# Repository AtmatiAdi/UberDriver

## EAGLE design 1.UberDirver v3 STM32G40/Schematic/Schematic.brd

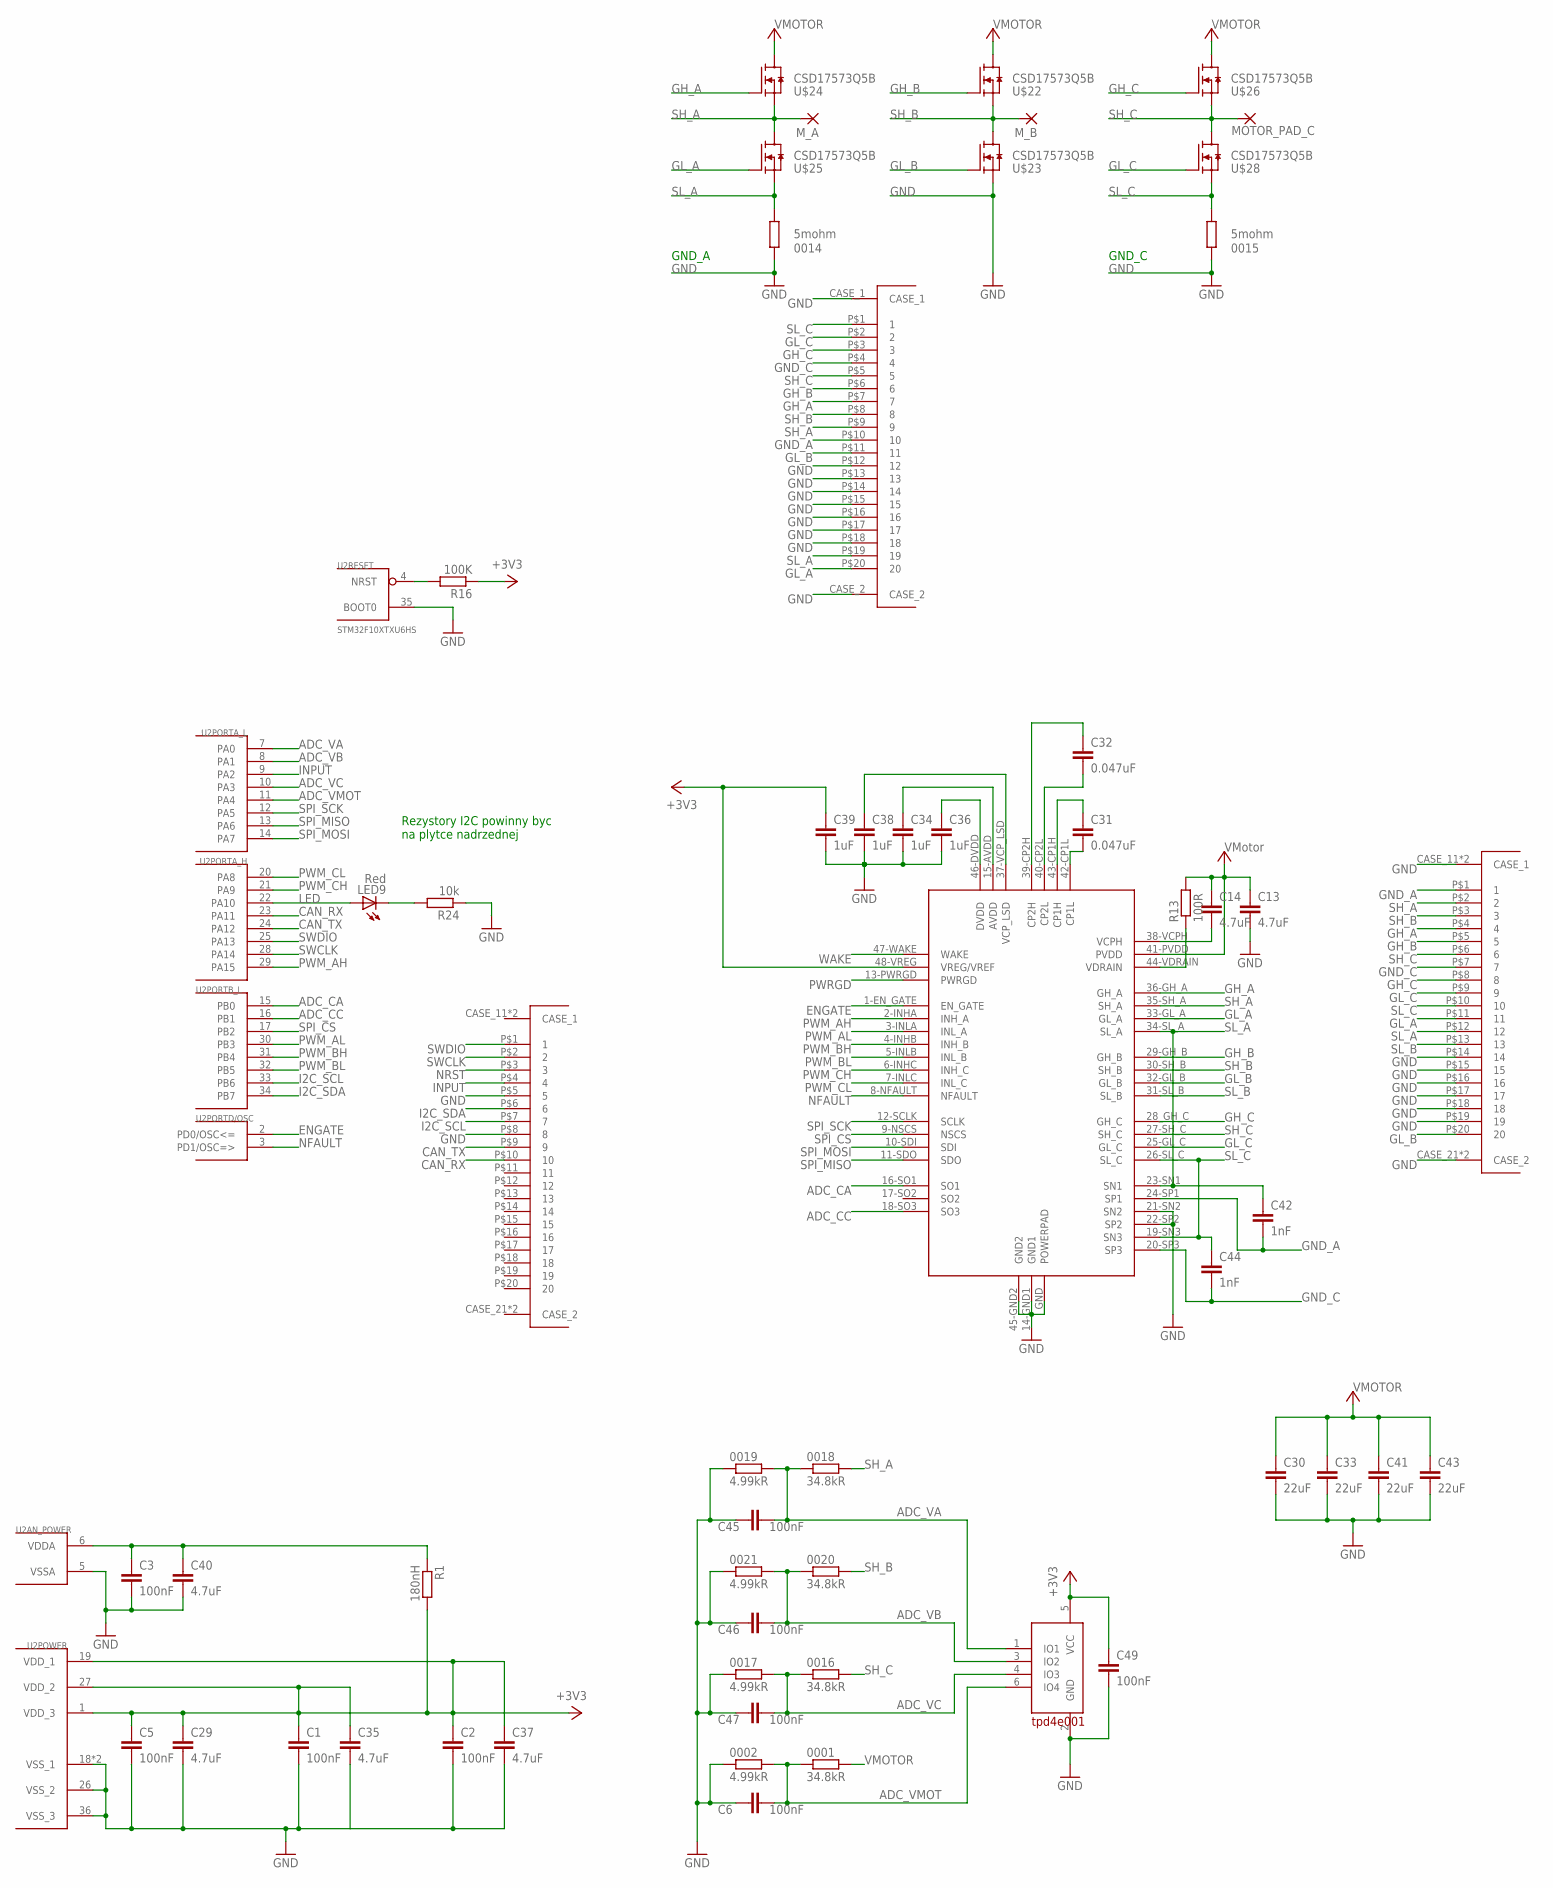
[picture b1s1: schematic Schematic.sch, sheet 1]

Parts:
0001, 0016, 0018, 0020: 34.8kR; R0402
0002, 0017, 0019, 0021: 4.99kR; R0402
0014, 0015: 5mohm; R2512
C1, C2, C3, C5, C6, C45, C46, C47, C49: 100nF; R0402
C13, C14: 4.7uF; C0805
C29, C35, C37, C40: 4.7uF; R0402
C30, C33, C41, C43: 22uF; C1206
C31, C32: 0.047uF; R0402
C34, C36, C38, C39: 1uF; R0402
C42, C44: 1nF; R0402
LED9: Red; SML0603
MOTOR_PAD_C: SMD5; SMD2,54-5,08
M_A: SMD5; SMD2,54-5,08
M_B: SMD5; SMD2,54-5,08
R1: 180nH; R0603
R13: 100R; R0603
R16: 100K; R0402
R24: 10k; R0402
U2: STM32F10XTXU6HS; VFQFPN36-HS
U$1, U$32: RECEPTACLE_20_0.4_5024262030
U$21: DRV8305; S-PQFP-G48
U$22, U$23, U$24, U$25, U$26, U$28: CSD17573Q5B; Q5B
U$30: PLUG_20_0.4_5024302012
U$31: TPD4E001; SOT-23

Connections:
+3V3: C1.1, C2.1, C5.1, C29.1, C35.1, C37.1, C39.1, C49.1, R1.2, R16.1, U2.1 (VDD_3), U2.19 (VDD_1), U2.27 (VDD_2), U$21.48-VREG (VREG/VREF), U$31.5 (VCC)
ADC_CA: U2.15 (PB0), U$21.16-SO1 (SO1)
ADC_CC: U2.16 (PB1), U$21.18-SO3 (SO3)
ADC_VA: 0018.1, 0019.2, C45.1, U2.7 (PA0), U$31.1 (IO1)
ADC_VB: 0020.1, 0021.2, C46.1, U2.8 (PA1), U$31.3 (IO2)
ADC_VC: 0016.1, 0017.2, C47.1, U2.10 (PA3), U$31.4 (IO3)
ADC_VMOT: 0001.1, 0002.2, C6.1, U2.11 (PA4), U$31.6 (IO4)
CAN_RX: U2.23 (PA11), U$1.P$10 (10)
CAN_TX: U2.24 (PA12), U$1.P$9 (9)
ENGATE: U2.2 (PD0/OSC<=), U$21.1-EN_GATE (EN_GATE)
GH_A: U$21.36-GH_A (GH_A), U$24.G, U$30.P$7 (7), U$32.P$4 (4)
GH_B: U$21.29-GH_B (GH_B), U$22.G, U$30.P$6 (6), U$32.P$5 (5)
GH_C: U$21.28_GH_C (GH_C), U$26.G, U$30.P$3 (3), U$32.P$8 (8)
GL_A: U$21.33-GL_A (GL_A), U$25.G, U$30.P$20 (20), U$32.P$11 (11)
GL_B: U$21.32-GL_B (GL_B), U$23.G, U$30.P$11 (11), U$32.P$20 (20)
GL_C: U$21.25-GL_C (GL_C), U$28.G, U$30.P$2 (2), U$32.P$9 (9)
GND: 0002.1, 0014.1, 0015.1, 0017.1, 0019.1, 0021.1, C1.2, C2.2, C3.2, C5.2, C6.2, C13.2, C29.2, C30.2, C33.2, C34.2, C35.2, C36.2, C37.2, C38.2, C39.2, C40.2, C41.2, C43.2, C45.2, C46.2, C47.2, C49.2, R24.1, U2.5 (VSSA), U2.18 (VSS_1), U2.26 (VSS_2), U2.35 (BOOT0), U2.36 (VSS_3), U2.GND (VSS_1), U$1.P$5 (5), U$1.P$8 (8), U$21.14-GND1 (GND1), U$21.21-SN2 (SN2), U$21.22-SP2 (SP2), U$21.45-GND2 (GND2), U$21.GND (POWERPAD), U$23.S, U$30.CASE_1, U$30.CASE_2, U$30.P$12 (12), U$30.P$13 (13), U$30.P$14 (14), U$30.P$15 (15), U$30.P$16 (16), U$30.P$17 (17), U$30.P$18 (18), U$31.2 (GND), U$32.CASE_11 (CASE_1), U$32.CASE_12 (CASE_1), U$32.CASE_21 (CASE_2), U$32.CASE_22 (CASE_2), U$32.P$14 (14), U$32.P$15 (15), U$32.P$16 (16), U$32.P$17 (17), U$32.P$18 (18), U$32.P$19 (19)
GND_A: C42.2, U$21.24-SP1 (SP1), U$30.P$10 (10), U$32.P$1 (1)
GND_C: C44.2, U$21.20-SP3 (SP3), U$30.P$4 (4), U$32.P$7 (7)
I2C_SCL: U2.33 (PB6), U$1.P$7 (7)
I2C_SDA: U2.34 (PB7), U$1.P$6 (6)
INPUT: U2.9 (PA2), U$1.P$4 (4)
LED: LED9.A, U2.22 (PA10)
unnamed: C3.1, C40.1, R1.1, U2.6 (VDDA)
unnamed: C36.1, U$21.46-DVDD (DVDD)
unnamed: C34.1, U$21.15-AVDD (AVDD)
unnamed: C38.1, U$21.37-VCP_LSD (VCP_LSD)
unnamed: C31.2, U$21.42-CP1L (CP1L)
unnamed: C31.1, U$21.43-CP1H (CP1H)
unnamed: C32.2, U$21.40-CP2L (CP2L)
unnamed: C32.1, U$21.39-CP2H (CP2H)
unnamed: R13.1, U$21.44-VDRAIN (VDRAIN)
unnamed: C14.2, U$21.38-VCPH (VCPH)
unnamed: LED9.C, R24.2
NFAULT: U2.3 (PD1/OSC=>), U$21.8-NFAULT (NFAULT)
NRST: R16.2, U2.4 (NRST), U$1.P$3 (3)
PWM_AH: U2.29 (PA15), U$21.2-INHA (INH_A)
PWM_AL: U2.30 (PB3), U$21.3-INLA (INL_A)
PWM_BH: U2.31 (PB4), U$21.4-INHB (INH_B)
PWM_BL: U2.32 (PB5), U$21.5-INLB (INL_B)
PWM_CH: U2.21 (PA9), U$21.6-INHC (INH_C)
PWM_CL: U2.20 (PA8), U$21.7-INLC (INL_C)
PWRGD: U$21.13-PWRGD (PWRGD)
SH_A: 0018.2, M_A.1, U$21.35-SH_A (SH_A), U$24.S, U$25.D, U$30.P$9 (9), U$32.P$2 (2)
SH_B: 0020.2, M_B.1, U$21.30-SH_B (SH_B), U$22.S, U$23.D, U$30.P$8 (8), U$32.P$3 (3)
SH_C: 0016.2, MOTOR_PAD_C.1, U$21.27-SH_C (SH_C), U$26.S, U$28.D, U$30.P$5 (5), U$32.P$6 (6)
SL_A: 0014.2, C42.1, U$21.23-SN1 (SN1), U$21.34-SL_A (SL_A), U$25.S, U$30.P$19 (19), U$32.P$12 (12)
SL_B: U$21.31-SL_B (SL_B), U$32.P$13 (13)
SL_C: 0015.2, C44.1, U$21.19-SN3 (SN3), U$21.26-SL_C (SL_C), U$28.S, U$30.P$1 (1), U$32.P$10 (10)
SPI_CS: U2.17 (PB2), U$21.9-NSCS (NSCS)
SPI_MISO: U2.13 (PA6), U$21.11-SDO (SDO)
SPI_MOSI: U2.14 (PA7), U$21.10-SDI (SDI)
SPI_SCK: U2.12 (PA5), U$21.12-SCLK (SCLK)
SWCLK: U2.28 (PA14), U$1.P$2 (2)
SWDIO: U2.25 (PA13), U$1.P$1 (1)
VMOTOR: 0001.2, C13.1, C14.1, C30.1, C33.1, C41.1, C43.1, R13.2, U$21.41-PVDD (PVDD), U$22.D, U$24.D, U$26.D
WAKE: U$21.47-WAKE (WAKE)

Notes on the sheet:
Rezystory I2C powinny byc na plytce nadrzednej
GND_A
GND_C

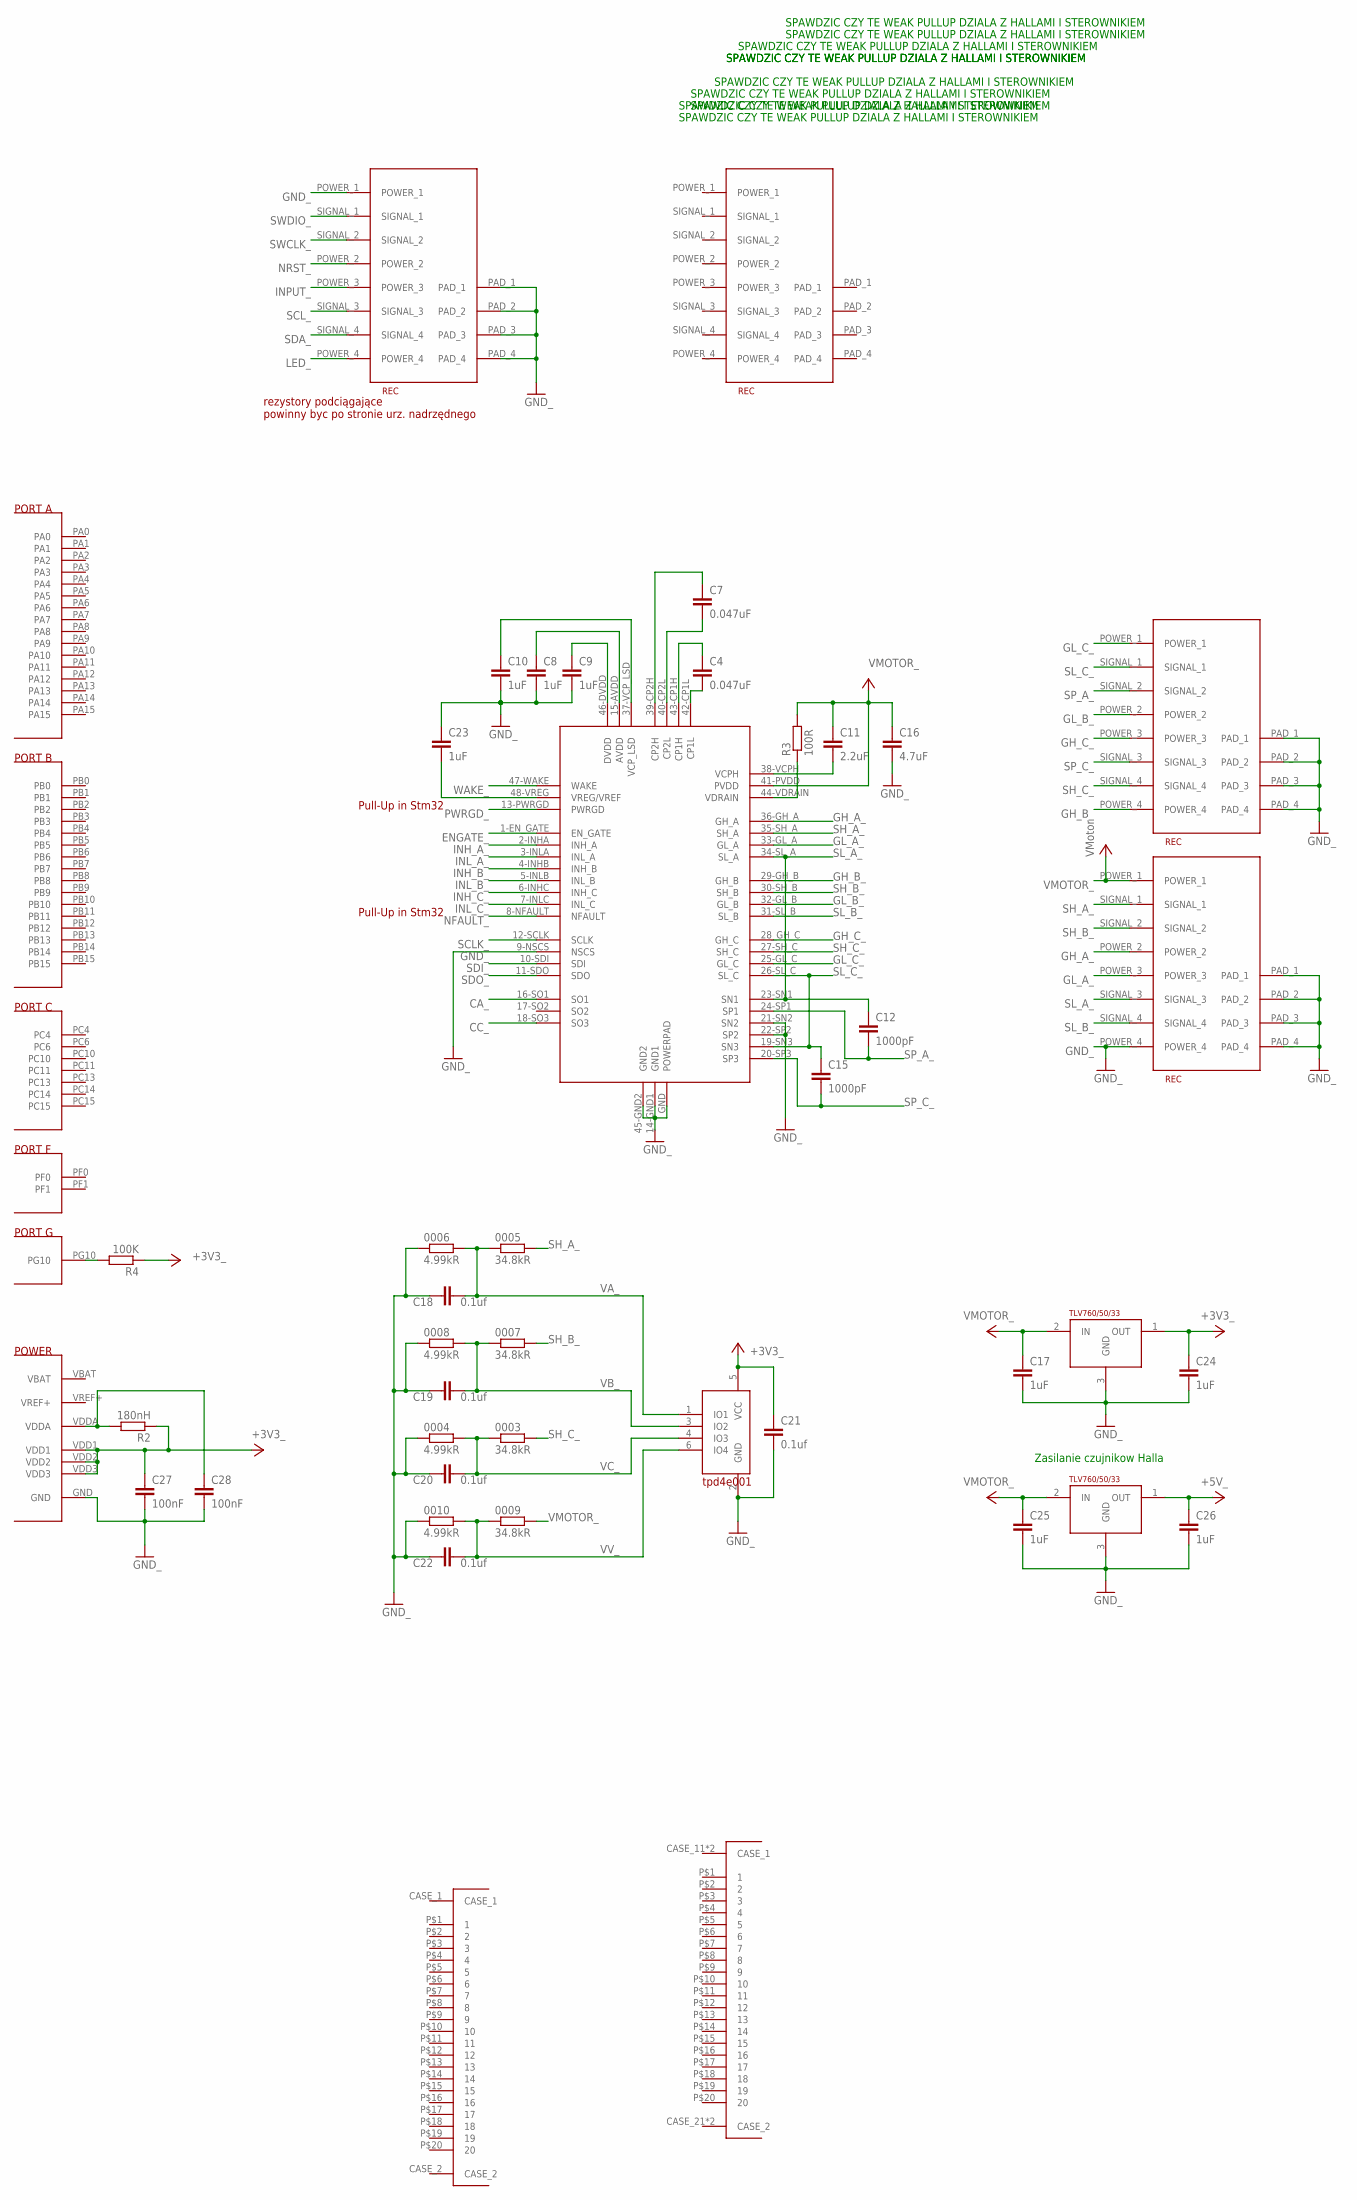
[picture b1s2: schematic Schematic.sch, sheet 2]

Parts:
0003, 0005, 0007, 0009: 34.8kR; R0402
0004, 0006, 0008, 0010: 4.99kR; R0402
C4, C7: 0.047uF; C0603
C8, C9, C10, C17, C23, C24, C25, C26: 1uF; C0603
C11: 2.2uF; C0603
C12, C15: 1000pF; C0603
C16: 4.7uF; C0805
C18, C19, C20, C22: 0.1uf; C0402
C21: 0.1uf; C0603
C27, C28: 100nF; C0603
R2: 180nH; R0603
R3: 100R; R0603
R4: 100K; R0603
U$12: STM32G473CC; VFQFPN36
U$13: DRV8305; S-PQFP-G48
U$14, U$15, U$18, U$19: MOLEG_REC_8X0.4MM; REC
U$16: TPD4E001; SOT-23
U$17, U$20: TLV760XX; SOT-23-3
U$27: PLUG_20_0.4_5024302012
U$29: RECEPTACLE_20_0.4_5024262030

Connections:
+3V3_: C21.1, C24.1, C27.1, R2.1, R4.1, U$12.VDD1, U$12.VDD2, U$12.VDD3, U$16.5 (VCC), U$17.1 (OUT)
+5V_: C26.1, U$20.1 (OUT)
CA_: U$13.16-SO1 (SO1)
CC_: U$13.18-SO3 (SO3)
ENGATE_: U$13.1-EN_GATE (EN_GATE)
GH_A_: U$13.36-GH_A (GH_A), U$15.POWER_2
GH_B_: U$13.29-GH_B (GH_B), U$14.POWER_4
GH_C_: U$13.28_GH_C (GH_C), U$14.POWER_3
GL_A_: U$13.33-GL_A (GL_A), U$15.POWER_3
GL_B_: U$13.32-GL_B (GL_B), U$14.POWER_2
GL_C_: U$13.25-GL_C (GL_C), U$14.POWER_1
GND_: 0004.1, 0006.1, 0008.1, 0010.1, C8.2, C9.2, C10.2, C16.2, C17.2, C18.2, C19.2, C20.2, C21.2, C22.2, C23.1, C24.2, C25.2, C26.2, C27.2, C28.2, U$12.GND, U$13.9-NSCS (NSCS), U$13.14-GND1 (GND1), U$13.21-SN2 (SN2), U$13.22-SP2 (SP2), U$13.45-GND2 (GND2), U$13.GND (POWERPAD), U$14.PAD_1, U$14.PAD_2, U$14.PAD_3, U$14.PAD_4, U$15.PAD_1, U$15.PAD_2, U$15.PAD_3, U$15.PAD_4, U$15.POWER_4, U$16.2 (GND), U$17.3 (GND), U$18.PAD_1, U$18.PAD_2, U$18.PAD_3, U$18.PAD_4, U$18.POWER_1, U$20.3 (GND)
INH_A_: U$13.2-INHA (INH_A)
INH_B_: U$13.4-INHB (INH_B)
INH_C_: U$13.6-INHC (INH_C)
INL_A_: U$13.3-INLA (INL_A)
INL_B_: U$13.5-INLB (INL_B)
INL_C_: U$13.7-INLC (INL_C)
INPUT_: U$18.POWER_3
LED_: U$18.POWER_4
unnamed: C9.1, U$13.46-DVDD (DVDD)
unnamed: C8.1, U$13.15-AVDD (AVDD)
unnamed: C10.1, U$13.37-VCP_LSD (VCP_LSD)
unnamed: C4.2, U$13.42-CP1L (CP1L)
unnamed: C4.1, U$13.43-CP1H (CP1H)
unnamed: C7.2, U$13.40-CP2L (CP2L)
unnamed: C7.1, U$13.39-CP2H (CP2H)
unnamed: R3.1, U$13.44-VDRAIN (VDRAIN)
unnamed: C11.2, U$13.38-VCPH (VCPH)
unnamed: C23.2, U$13.48-VREG (VREG/VREF)
unnamed: R4.2, U$12.PG10
unnamed: C28.1, R2.2, U$12.VDDA
NFAULT_: U$13.8-NFAULT (NFAULT)
NRST_: U$18.POWER_2
PWRGD_: U$13.13-PWRGD (PWRGD)
SCLK_: U$13.12-SCLK (SCLK)
SCL_: U$18.SIGNAL_3
SDA_: U$18.SIGNAL_4
SDI_: U$13.10-SDI (SDI)
SDO_: U$13.11-SDO (SDO)
SH_A_: 0005.2, U$13.35-SH_A (SH_A), U$15.SIGNAL_1
SH_B_: 0007.2, U$13.30-SH_B (SH_B), U$15.SIGNAL_2
SH_C_: 0003.2, U$13.27-SH_C (SH_C), U$14.SIGNAL_4
SL_A_: C12.1, U$13.23-SN1 (SN1), U$13.34-SL_A (SL_A), U$15.SIGNAL_3
SL_B_: U$13.31-SL_B (SL_B), U$15.SIGNAL_4
SL_C_: C15.1, U$13.19-SN3 (SN3), U$13.26-SL_C (SL_C), U$14.SIGNAL_1
SP_A_: C12.2, U$13.24-SP1 (SP1), U$14.SIGNAL_2
SP_C_: C15.2, U$13.20-SP3 (SP3), U$14.SIGNAL_3
SWCLK_: U$18.SIGNAL_2
SWDIO_: U$18.SIGNAL_1
VA_: 0005.1, 0006.2, C18.1, U$16.1 (IO1)
VB_: 0007.1, 0008.2, C19.1, U$16.3 (IO2)
VC_: 0003.1, 0004.2, C20.1, U$16.4 (IO3)
VMOTOR_: 0009.2, C11.1, C16.1, C17.1, C25.1, R3.2, U$13.41-PVDD (PVDD), U$15.POWER_1, U$17.2 (IN), U$20.2 (IN)
VV_: 0009.1, 0010.2, C22.1, U$16.6 (IO4)
WAKE_: U$13.47-WAKE (WAKE)

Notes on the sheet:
Pull-Up in Stm32
rezystory podciągające powinny byc po stronie urz. nadrzędnego
Zasilanie czujnikow Halla
SPAWDZIC CZY TE WEAK PULLUP DZIALA Z HALLAMI I STEROWNIKIEM

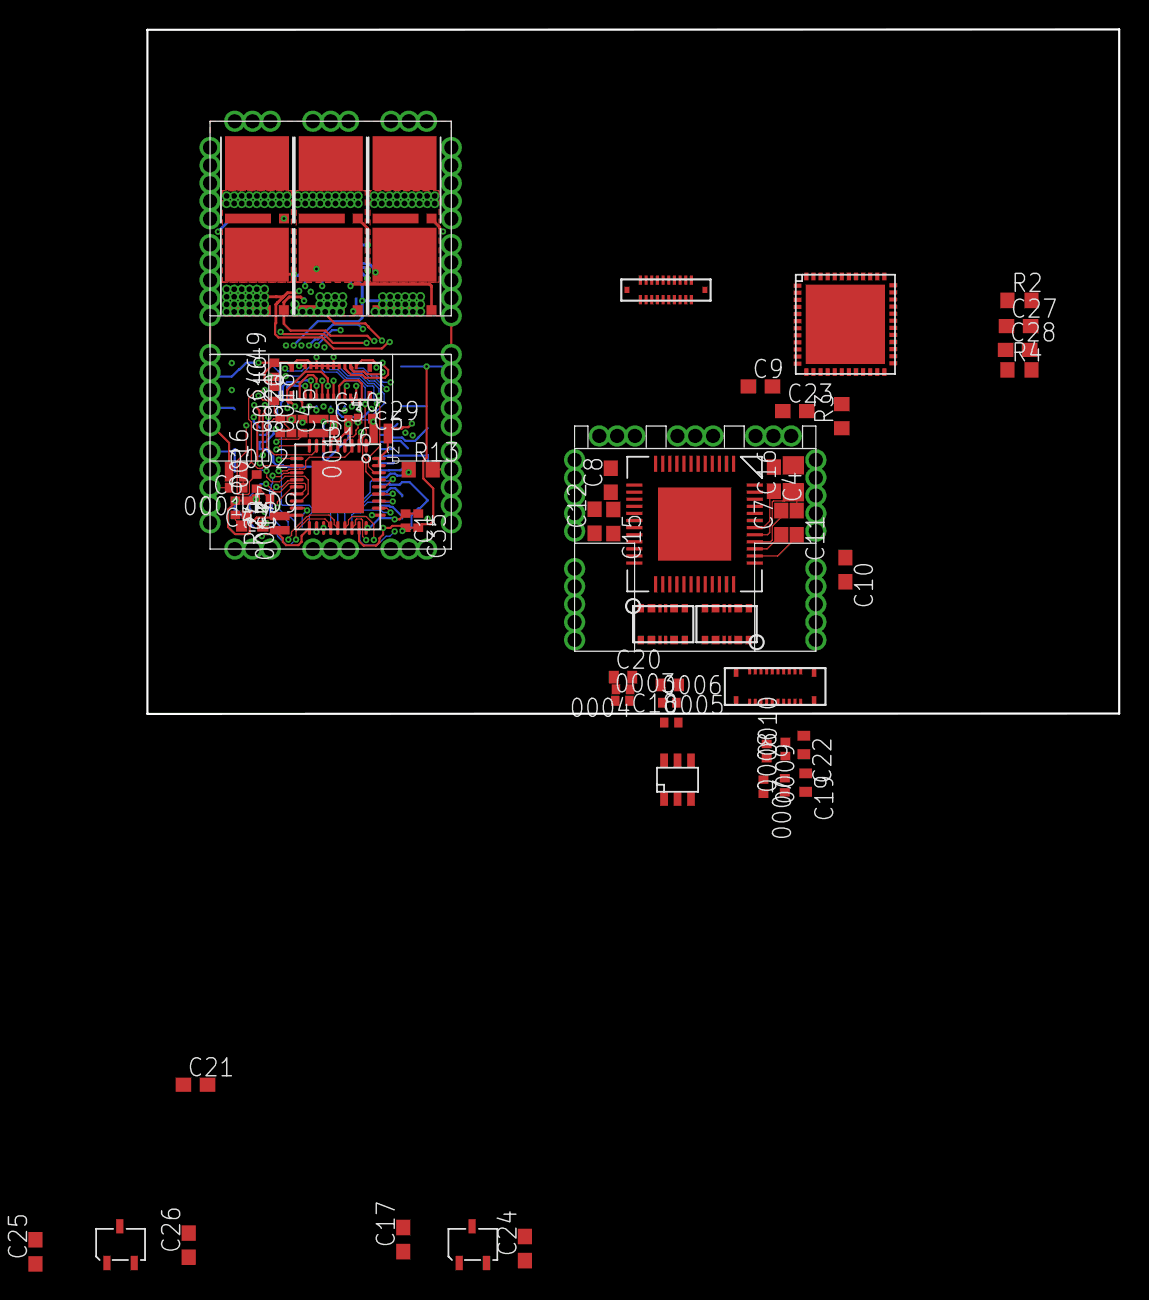
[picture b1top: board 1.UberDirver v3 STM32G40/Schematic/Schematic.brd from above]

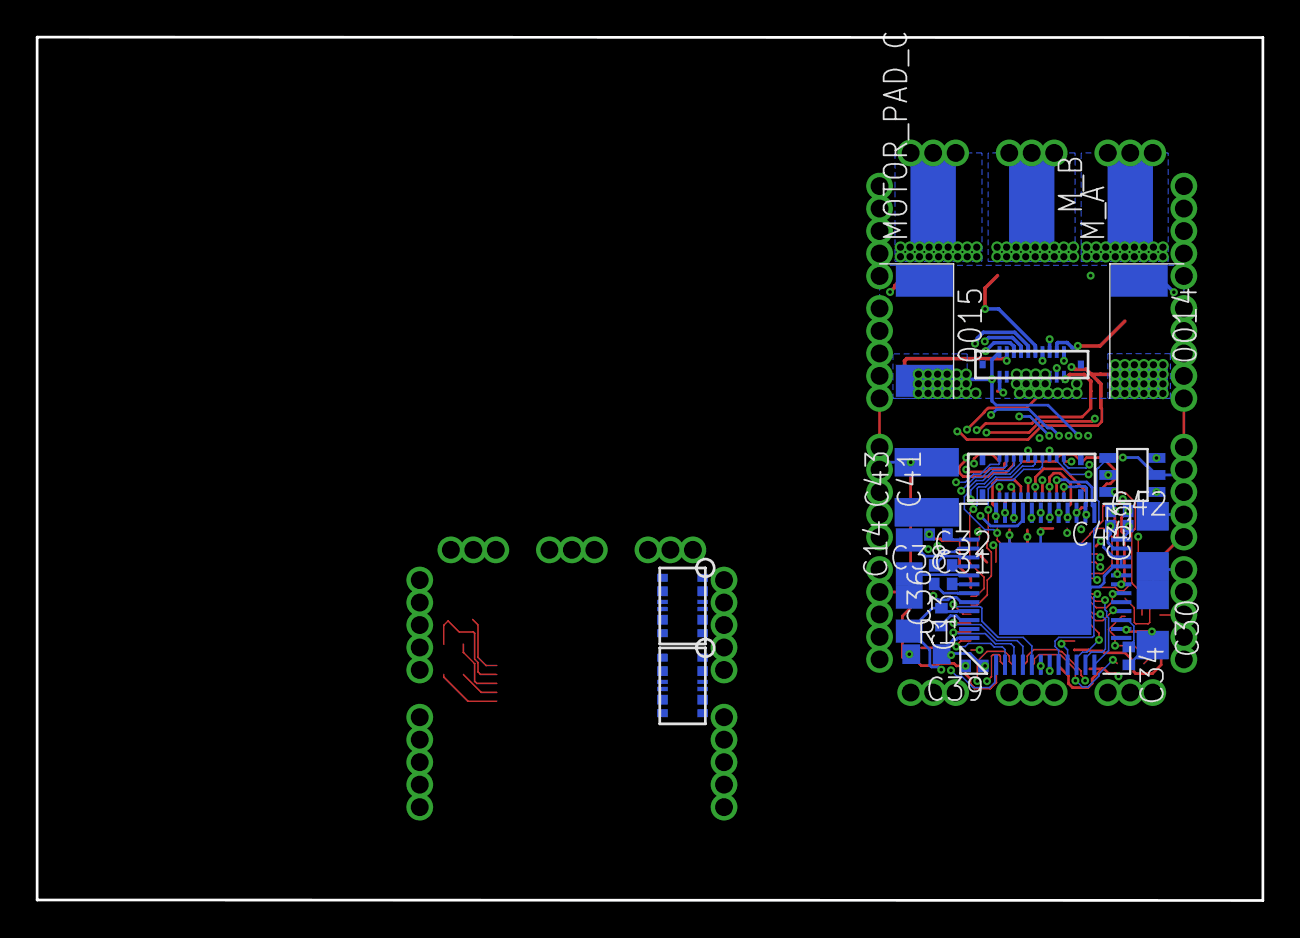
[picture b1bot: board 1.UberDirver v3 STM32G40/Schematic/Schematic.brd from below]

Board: 4 copper layers, 68.6 x 48.3 mm, 100 parts (26 on the bottom side), 89 nets.

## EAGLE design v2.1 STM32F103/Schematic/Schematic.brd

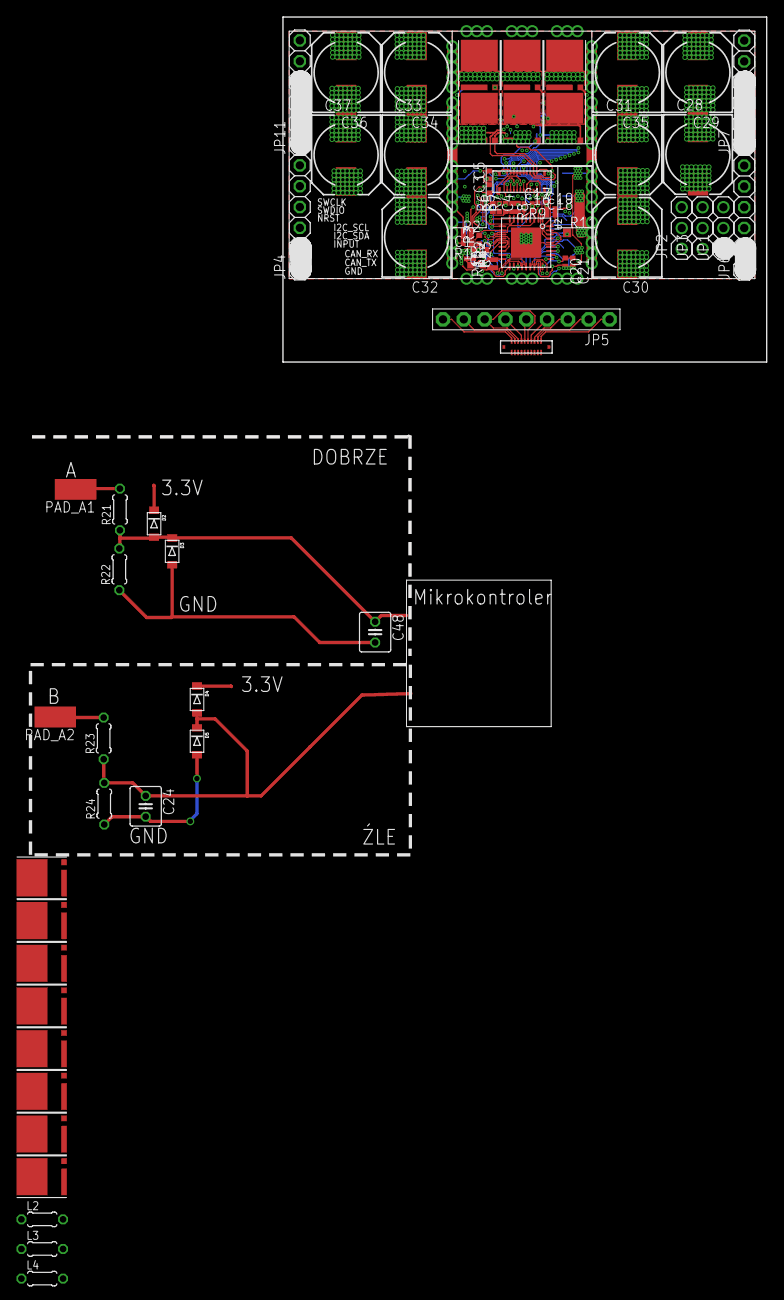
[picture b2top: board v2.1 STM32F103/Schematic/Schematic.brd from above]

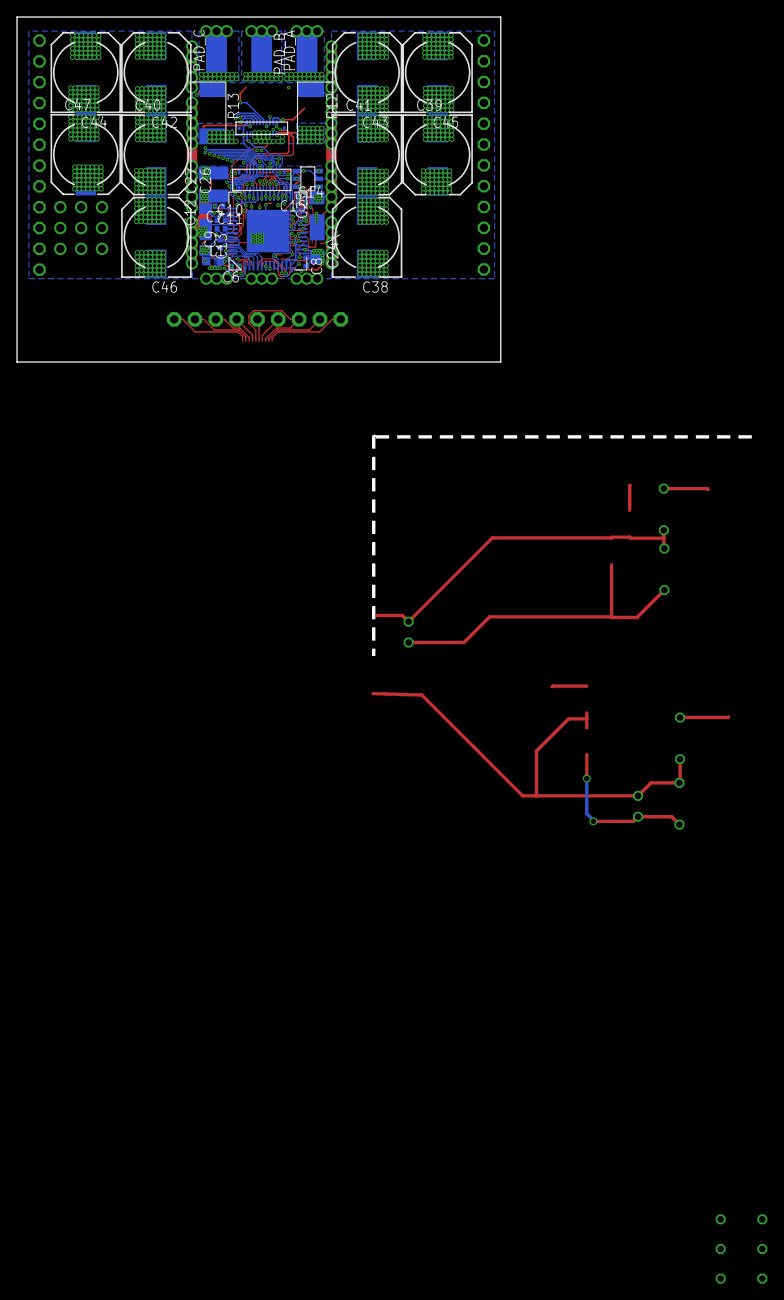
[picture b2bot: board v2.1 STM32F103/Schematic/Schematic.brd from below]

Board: 4 copper layers, 89.6 x 77.9 mm, 109 parts (34 on the bottom side), 76 nets.

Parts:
C1, C2, C3, C4, C14, C15: 1nF; R0402
C5, C16, C18, C20, C22: 100nF; R0402
C6, C7, C8, C9: 1uF; R0402
C10, C11: 0.047uF; R0402
C12, C13: 4.7uF; C0805
C17, C19, C21, C23: 4.7uF; R0402
C24, C48: C025-040X050
C24\, C25, C26, C27: 22uF; C1206
C28, C29, C30, C31, C32, C33, C34, C35, C36, C37, C38, C39, C40, C41, C42, C43, C44, C45, C46, C47: 220uf; 150CLZ-0810
D1: Red; SML0603
D2, D3, D4, D5: SOD-123FL
JP1, JP2, JP3: 1X03
JP4, JP6, JP7, JP11: 1X06
JP5: 1X09-BIG
L1: 1mH; R0603
L2, L3, L4: 0204/5
PAD_A, PAD_A1, PAD_A2: SMD2,54-5,08
PAD_B: SMD2,54-5,08
PAD_C: SMD2,54-5,08
Q1, Q2, Q3, Q4, Q5, Q6, Q7, Q8, Q9, Q10, Q11, Q12, Q13, Q14: CSD17573Q5B; Q5B
R1, R3, R5, R7: 100k; R0402
R2, R4, R6, R8: 4.99kR; R0402
R9: 100K; R0402
R10: 10k; R0402
R11: 100R; R0603
R12, R13: 5mohm; R2512
R21, R22, R23, R24: 0204/5
U2: STM32F10XTXU6HS; VFQFPN36-HS
U$1, U$32: RECEPTACLE_20_0.4_5024262030
U$2, U$30: PLUG_20_0.4_5024302012
U$21: DRV8305; S-PQFP-G48
U$31: TPD4E001; SOT-23

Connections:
+3V3: C5.1, C6.1, C18.1, C19.1, C20.1, C21.1, C22.1, C23.1, L1.2, R9.1, U2.1, U2.19, U2.27, U$21.48-VREG, U$31.5
+VCC: Q9.D, Q10.D, Q11.D
ADC_CA: U2.15, U$21.16-SO1
ADC_CC: U2.16, U$21.18-SO3
ADC_VA: C4.1, R7.1, R8.2, U2.7, U$31.1
ADC_VB: C3.1, R5.1, R6.2, U2.8, U$31.3
ADC_VC: C2.1, R3.1, R4.2, U2.10, U$31.4
ADC_VMOT: C1.1, R1.1, R2.2, U2.11, U$31.6
CAN_RX: JP1.3, U2.23, U$1.P$10
CAN_TX: JP1.2, U2.24, U$1.P$9
ENGATE: U2.2, U$21.1-EN_GATE
GH_A: Q1.G, U$21.36-GH_A, U$30.P$7, U$32.P$4
GH_B: Q3.G, U$21.29-GH_B, U$30.P$6, U$32.P$5
GH_C: Q5.G, U$21.28_GH_C, U$30.P$3, U$32.P$8
GL_A: Q2.G, U$21.33-GL_A, U$30.P$20, U$32.P$11
GL_B: Q4.G, U$21.32-GL_B, U$30.P$11, U$32.P$20
GL_C: Q6.G, U$21.25-GL_C, U$30.P$2, U$32.P$9
GND: C1.2, C2.2, C3.2, C4.2, C5.2, C6.2, C7.2, C8.2, C9.2, C13.2, C16.2, C17.2, C18.2, C19.2, C20.2, C21.2, C22.2, C23.2, C24\.2, C25.2, C26.2, C27.2, C28.-, C29.-, C30.-, C31.-, C32.-, C33.-, C34.-, C35.-, C36.-, C37.-, C38.-, C39.-, C40.-, C41.-, C42.-, C43.-, C44.-, C45.-, C46.-, C47.-, JP1.1, JP4.1, JP4.2, JP6.1, JP6.2, JP7.1, JP7.2, JP7.3, JP7.4, JP11.1, JP11.2, JP11.3, JP11.4, Q4.S, Q8.S, Q12.S, Q13.S, Q14.S, R2.1, R4.1, R6.1, R8.1, R10.1, R12.1, R13.1, U2.5, U2.18, U2.26, U2.35, U2.36, U2.GND, U$1.P$5, U$1.P$8, U$21.14-GND1, U$21.21-SN2, U$21.22-SP2, U$21.45-GND2, U$21.GND, U$30.CASE_1, U$30.CASE_2, U$30.P$12, U$30.P$13, U$30.P$14, U$30.P$15, U$30.P$16, U$30.P$17, U$30.P$18, U$31.2, U$32.CASE_11, U$32.CASE_12, U$32.CASE_21, U$32.CASE_22, U$32.P$14, U$32.P$15, U$32.P$16, U$32.P$17, U$32.P$18, U$32.P$19
GND_A: C14.2, U$21.24-SP1, U$30.P$10, U$32.P$1
GND_C: C15.2, U$21.20-SP3, U$30.P$4, U$32.P$7
I2C_SCL: JP3.3, U2.33, U$1.P$7
I2C_SDA: JP3.2, U2.34, U$1.P$6
INPUT: JP3.1, U2.9, U$1.P$4
LED: D1.A, U2.22
unnamed: JP5.9, U$2.P$1
unnamed: C16.1, C17.1, L1.1, U2.6
unnamed: JP5.8, U$2.P$2
unnamed: JP5.7, U$2.P$3, U$2.P$6
unnamed: JP5.6, U$2.P$4
unnamed: JP5.5, U$2.P$5
unnamed: JP5.2, U$2.P$9
unnamed: JP5.4, U$2.P$7
unnamed: JP5.3, U$2.P$8
unnamed: C9.1, U$21.46-DVDD
unnamed: JP5.1, U$2.P$10
unnamed: C8.1, U$21.15-AVDD
unnamed: C7.1, U$21.37-VCP_LSD
unnamed: C11.2, U$21.42-CP1L
unnamed: PAD_A1.1, R21.2
unnamed: C11.1, U$21.43-CP1H
unnamed: C48.1, D2.A, D3.C, R21.1, R22.2
unnamed: C48.2, D3.A, R22.1
unnamed: PAD_A2.1, R23.2
unnamed: C10.2, U$21.40-CP2L
unnamed: C10.1, U$21.39-CP2H
unnamed: R11.1, U$21.44-VDRAIN
unnamed: C12.2, U$21.38-VCPH
unnamed: C24.1, D4.A, D5.C, R23.1, R24.2
unnamed: C24.2, D5.A, R24.1
unnamed: Q7.S, Q8.D
unnamed: L2.1, Q9.S, Q12.D
unnamed: L4.1, Q10.S, Q13.D
unnamed: L3.1, Q11.S, Q14.D
unnamed: L2.2, L3.2, L4.2
unnamed: D1.C, R10.2
NFAULT: U2.3, U$21.8-NFAULT
NRST: JP2.1, R9.2, U2.4, U$1.P$3
PWM_AH: U2.29, U$21.2-INHA
PWM_AL: U2.30, U$21.3-INLA
PWM_BH: U2.31, U$21.4-INHB
PWM_BL: U2.32, U$21.5-INLB
PWM_CH: U2.21, U$21.6-INHC
PWM_CL: U2.20, U$21.7-INLC
SH_A: PAD_A.1, Q1.S, Q2.D, R7.2, U$21.35-SH_A, U$30.P$9, U$32.P$2
SH_B: PAD_B.1, Q3.S, Q4.D, R5.2, U$21.30-SH_B, U$30.P$8, U$32.P$3
SH_C: PAD_C.1, Q5.S, Q6.D, R3.2, U$21.27-SH_C, U$30.P$5, U$32.P$6
SL_A: C14.1, Q2.S, R12.2, U$21.23-SN1, U$21.34-SL_A, U$30.P$19, U$32.P$12
SL_B: U$21.31-SL_B, U$32.P$13
SL_C: C15.1, Q6.S, R13.2, U$21.19-SN3, U$21.26-SL_C, U$30.P$1, U$32.P$10
SPI_CS: U2.17, U$21.9-NSCS
SPI_MISO: U2.13, U$21.11-SDO
SPI_MOSI: U2.14, U$21.10-SDI
SPI_SCK: U2.12, U$21.12-SCLK
SWCLK: JP2.3, U2.28, U$1.P$2
SWDIO: JP2.2, U2.25, U$1.P$1
VMOTOR: C12.1, C13.1, C24\.1, C25.1, C26.1, C27.1, C28.+, C29.+, C30.+, C31.+, C32.+, C33.+, C34.+, C35.+, C36.+, C37.+, C38.+, C39.+, C40.+, C41.+, C42.+, C43.+, C44.+, C45.+, C46.+, C47.+, JP4.3, JP4.4, JP4.5, JP4.6, JP6.3, JP6.4, JP6.5, JP6.6, JP7.5, JP7.6, JP11.5, JP11.6, Q1.D, Q3.D, Q5.D, R1.2, R11.2, U$21.41-PVDD

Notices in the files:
parts and their libraries:
microbuilder: This work is placed in the public domain, and may be freely used for commercial and non-commercial work with the following conditions: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
SparkFun-Coils: Licensing: Creative Commons ShareAlike 4.0 International - https://creativecommons.org/licenses/by-sa/4.0
